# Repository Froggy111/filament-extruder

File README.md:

# Filament Extruder

fully closed loop FDM filameent production machine

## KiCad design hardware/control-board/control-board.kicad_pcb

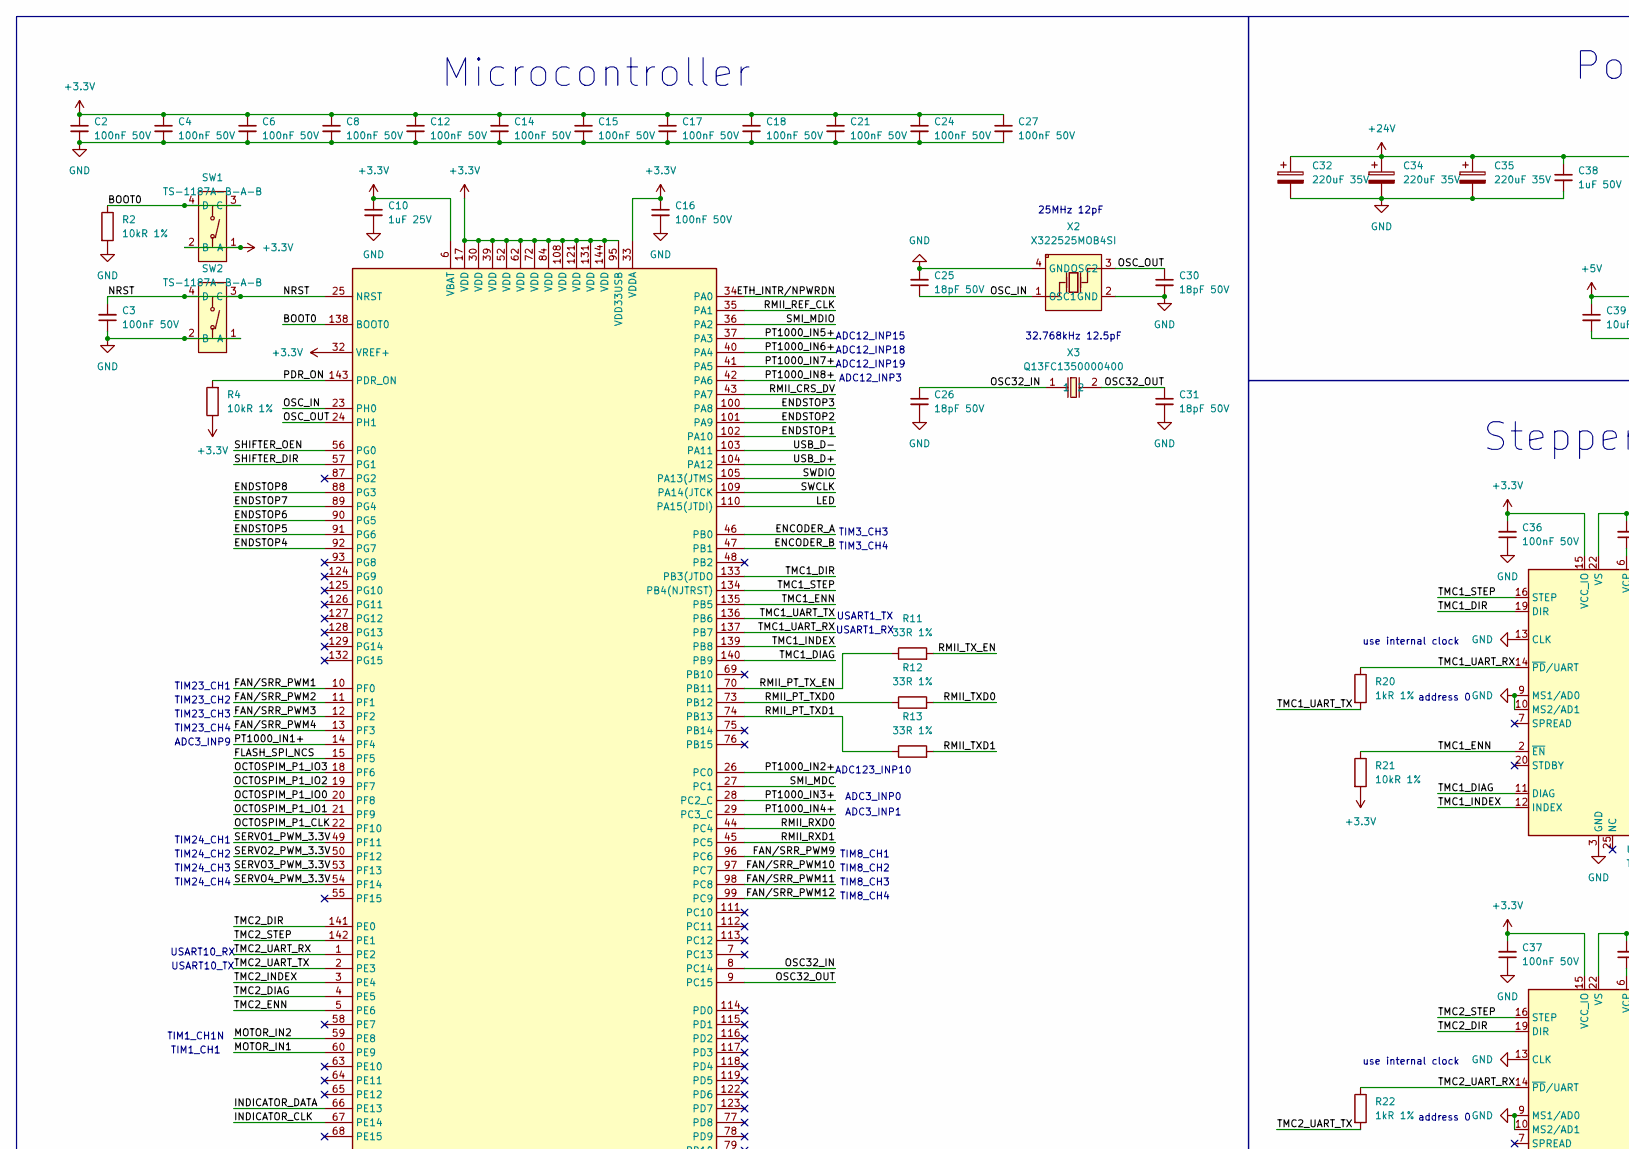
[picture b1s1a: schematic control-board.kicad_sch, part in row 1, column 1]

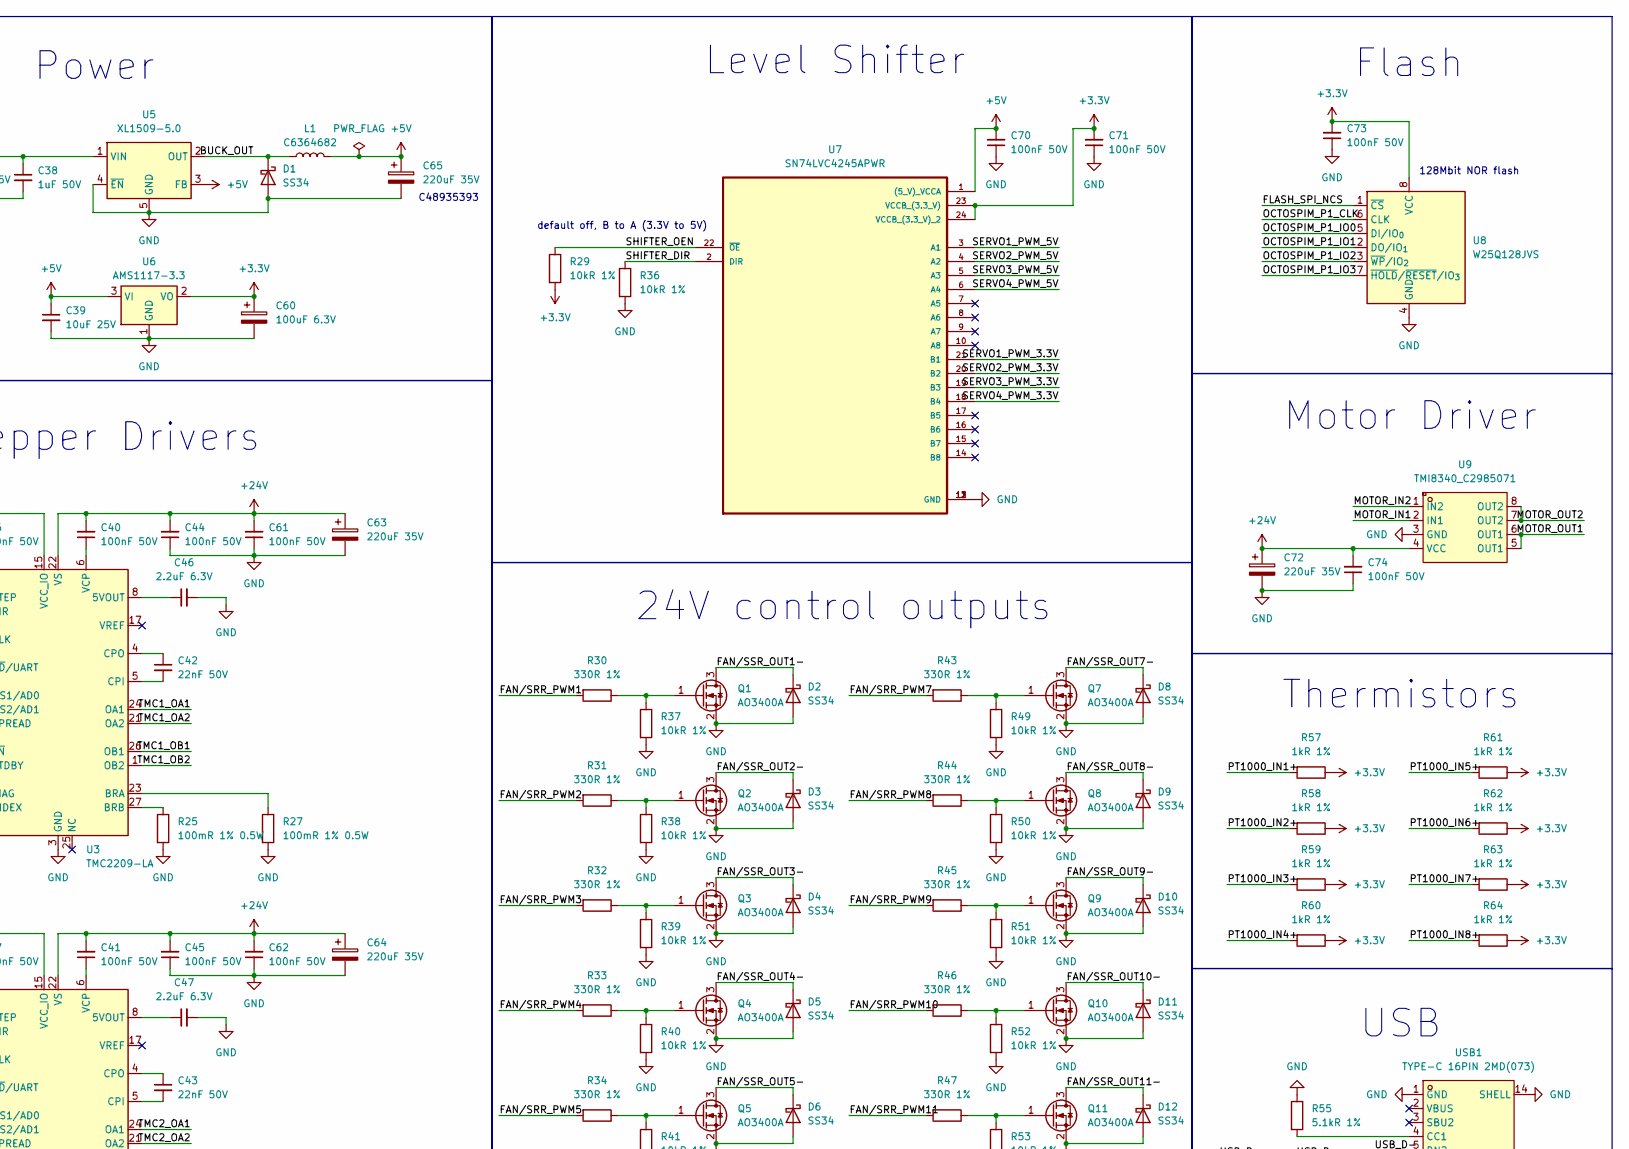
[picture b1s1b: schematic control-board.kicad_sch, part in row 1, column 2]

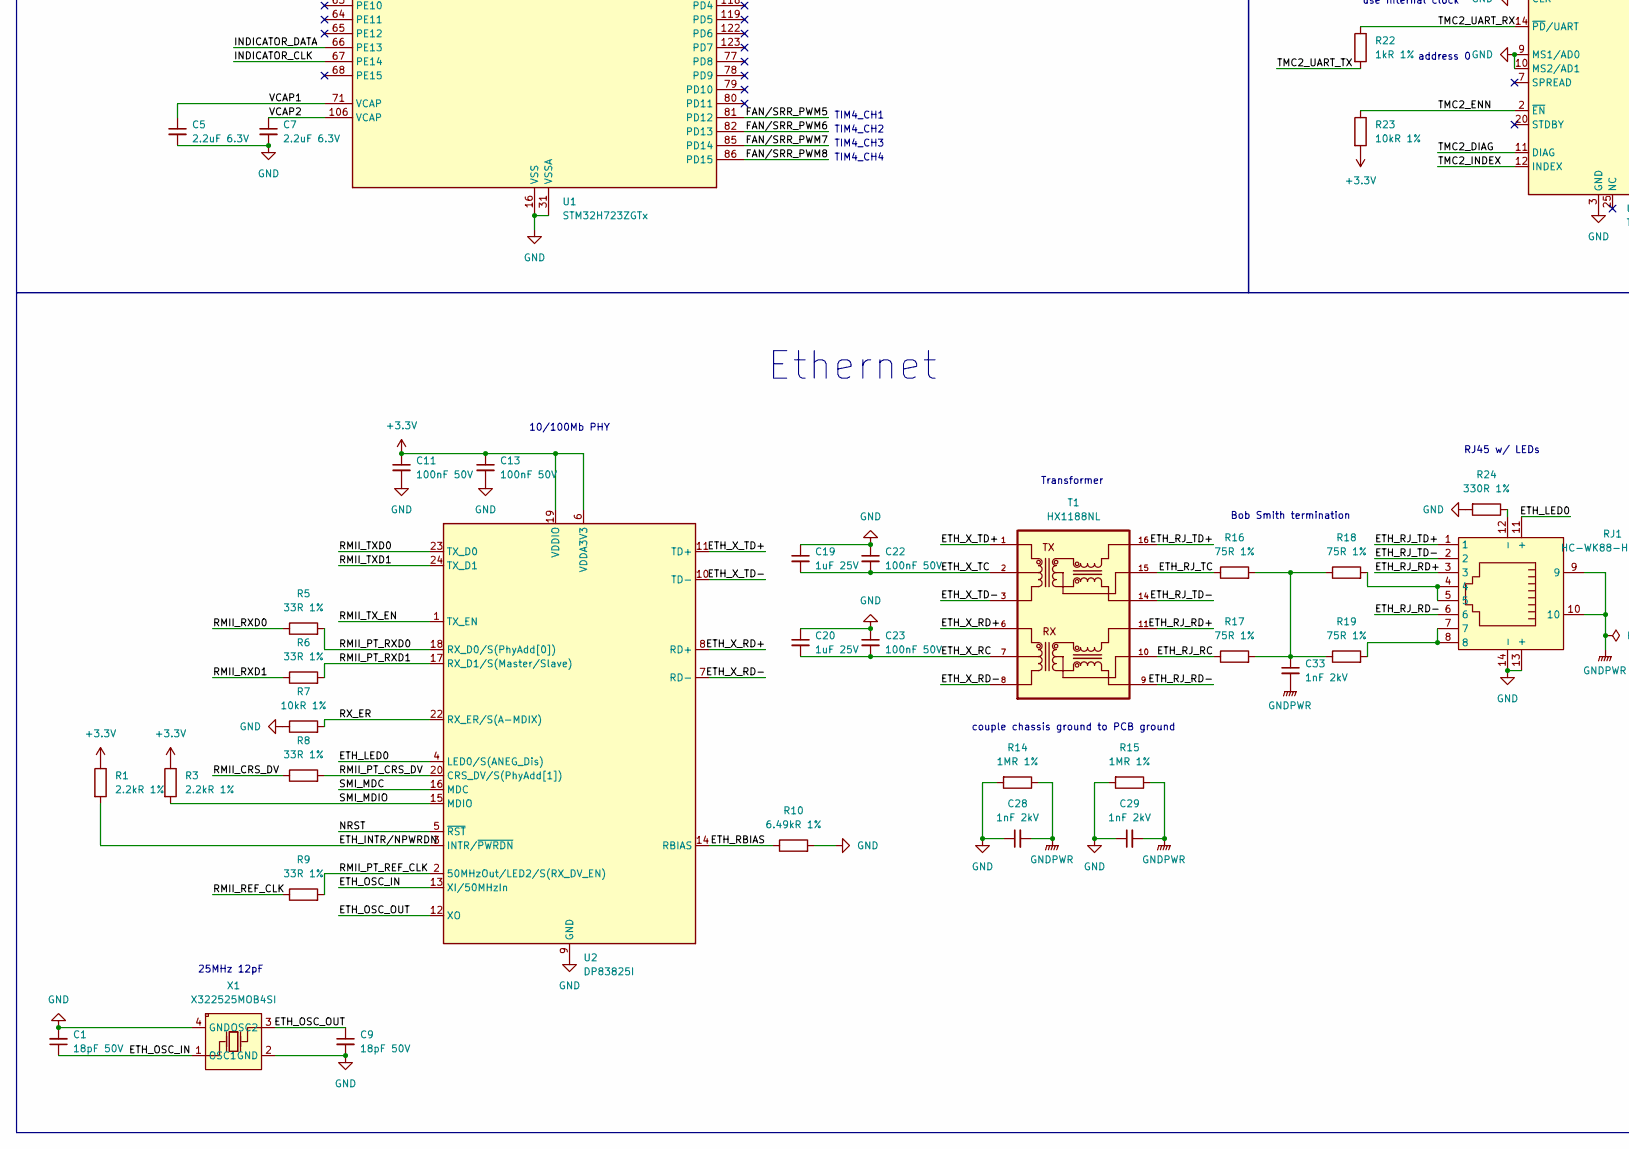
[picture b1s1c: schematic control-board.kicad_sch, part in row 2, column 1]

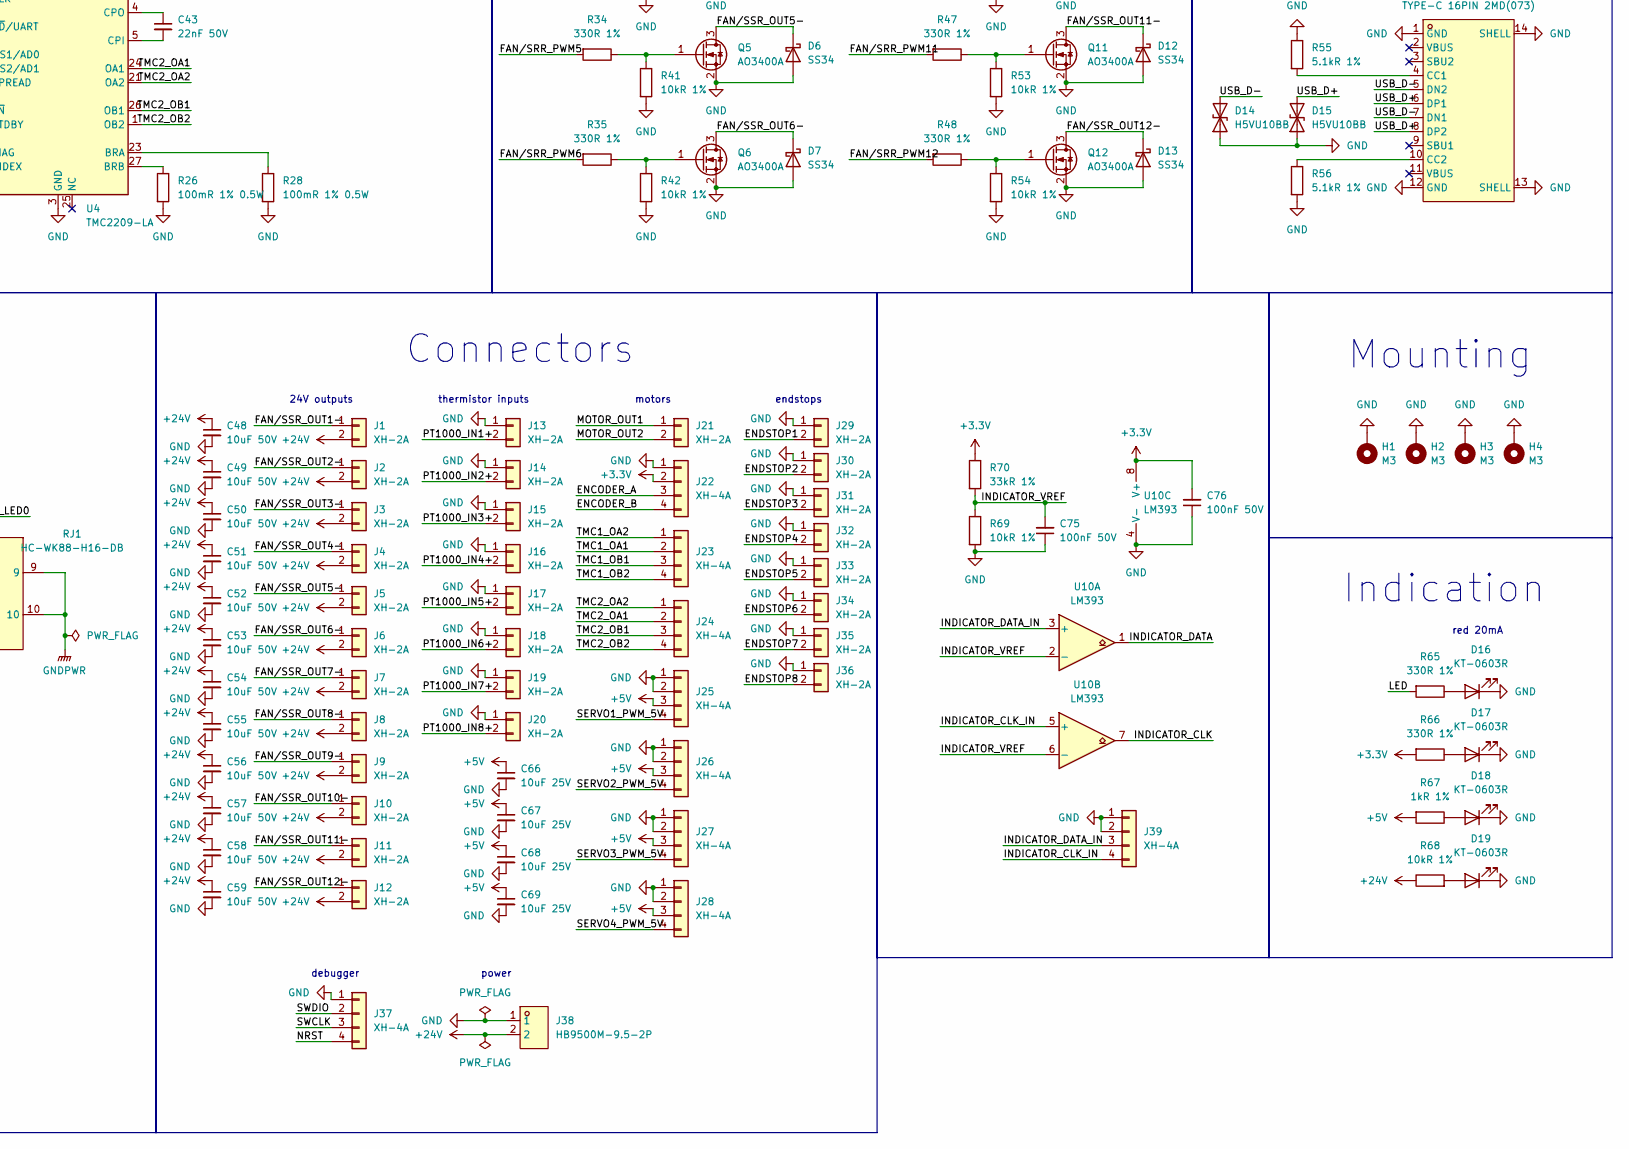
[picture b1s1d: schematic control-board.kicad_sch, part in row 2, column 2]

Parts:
C1, C9, C25, C26, C30, C31: 18pF 50V; C_0402_1005Metric
C2, C3, C4, C6, C8, C11, C12, C13, C14, C15, C16, C17, C18, C21, C22, C23, C24, C27, C36, C37, C40, C41, C44, C45, C61, C62, C70, C71, C73, C74, C75, C76: 100nF 50V; C_0402_1005Metric
C5, C7, C46, C47: 2.2uF 6.3V; C_0402_1005Metric
C10, C19, C20: 1uF 25V; C_0402_1005Metric
C28, C29, C33: 1nF 2kV; C_1206_3216Metric
C32, C34, C35, C63, C64, C65, C72: 220uF 35V; CP_Elec_8x10.5
C38: 1uF 50V; C_0603_1608Metric
C39, C66, C67, C68, C69: 10uF 25V; C_0603_1608Metric
C42, C43: 22nF 50V; C_0402_1005Metric
C48, C49, C50, C51, C52, C53, C54, C55, C56, C57, C58, C59: 10uF 50V; C_1206_3216Metric
C60: 100uF 6.3V; CP_EIA-3528-21_Kemet-B
D1, D2, D3, D4, D5, D6, D7, D8, D9, D10, D11, D12, D13: SS34; D_SMA
D14, D15: H5VU10BB; D_SOD-882
D16, D17, D18, D19: KT-0603R; LED_0603_1608Metric
H1, H2, H3, H4: M3; MountingHole_3.2mm_M3_Pad_Via
J1, J2, J3, J4, J5, J6, J7, J8, J9, J10, J11, J12, J13, J14, J15, J16, J17, J18, J19, J20, J21, J29, J30, J31, J32, J33, J34, J35, J36: XH-2A; JST_XH_B2B-XH-A_1x02_P2.50mm_Vertical
J22, J23, J24, J25, J26, J27, J28, J37, J39: XH-4A; JST_XH_B4B-XH-A_1x04_P2.50mm_Vertical
J38: HB9500M-9.5-2P; CONN-TH_HB9500M-9.5-2P; LCSC Part C601239
L1: C6364682; L_Chilisin_BMRF00101040
Q1, Q2, Q3, Q4, Q5, Q6, Q7, Q8, Q9, Q10, Q11, Q12: AO3400A; SOT-23
R1, R3: 2.2kR 1%; R_0402_1005Metric
R2, R4, R7, R21, R23, R29, R36, R37, R38, R39, R40, R41, R42, R49, R50, R51, R52, R53, R54, R68, R69: 10kR 1%; R_0402_1005Metric
R5, R6, R8, R9, R11, R12, R13: 33R 1%; R_0402_1005Metric
R10: 6.49kR 1%; R_0402_1005Metric
R14, R15: 1MR 1%; R_1206_3216Metric
R16, R17, R18, R19: 75R 1%; R_0402_1005Metric
R20, R22, R57, R58, R59, R60, R61, R62, R63, R64, R67: 1kR 1%; R_0402_1005Metric
R24, R30, R31, R32, R33, R34, R35, R43, R44, R45, R46, R47, R48, R65, R66: 330R 1%; R_0402_1005Metric
R25, R26, R27, R28: 100mR 1% 0.5W; R_1206_3216Metric
R55, R56: 5.1kR 1%; R_0402_1005Metric
R70: 33kR 1%; R_0402_1005Metric
RJ1: HC-WK88-H16-DB; RJ45-TH_HC-WK88-H16-DB; LCSC Part C7501824
SW1, SW2: TS-1187A-B-A-B; SW-SMD_4P-L5.1-W5.1-P3.70-LS6.5-TL_H1.5; LCSC Part C318884
T1: HX1188NL; HXXXX
U1: STM32H723ZGTx; LQFP-144_20x20mm_P0.5mm
U2: DP83825I; Texas_RMQ0024A_WQFN-24-1EP_3x3mm_P0.4mm_EP1.9x1.9mm
U3, U4: TMC2209-LA; VQFN-28-1EP_5x5mm_P0.5mm_EP3.7x3.7mm_ThermalVias
U5: XL1509-5.0; SOIC-8_3.9x4.9mm_P1.27mm
U6: AMS1117-3.3; SOT-223-3_TabPin2
U7: SN74LVC4245APWR; SOP65P640X120-24N
U8: W25Q128JVS; SOIC-8_5.3x5.3mm_P1.27mm
U9: TMI8340_C2985071; SOP-8_L4.9-W3.9-P1.27-LS6.0-BL-1; LCSC Part C2985071
U10: LM393; SOIC-8_3.9x4.9mm_P1.27mm
USB1: TYPE-C 16PIN 2MD(073); USB-C-SMD_TYPE-C-6PIN-2MD-073; LCSC Part C2765186
X1, X2: X322525MOB4SI; CRYSTAL-SMD_4P-L3.2-W2.5-BL; LCSC Part C9006
X3: Q13FC1350000400; FC-135R_L3.2-W1.5; LCSC Part C32346

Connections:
+3.3V: C2.1, C4.1, C6.1, C8.1, C10.1, C11.1, C12.1, C13.1, C14.1, C15.1, C16.1, C17.1, C18.1, C21.1, C24.1, C27.1, C36.2, C37.2, C60.1, C71.2, C73.2, C76.2, J22.2, R1.1, R3.1, R4.1, R21.2, R23.2, R29.2, R57.1, R58.1, R59.1, R60.1, R61.1, R62.1, R63.1, R64.1, R66.2, R70.1, SW1.1 (A), SW1.2 (B), U1.6 (VBAT), U1.17 (VDD), U1.30 (VDD), U1.32 (VREF+), U1.33 (VDDA), U1.39 (VDD), U1.52 (VDD), U1.62 (VDD), U1.72 (VDD), U1.84 (VDD), U1.95 (VDD33USB), U1.108 (VDD), U1.121 (VDD), U1.131 (VDD), U1.144 (VDD), U2.6 (VDDA3V3), U2.19 (VDDIO), U3.15 (VCC_IO), U4.15 (VCC_IO), U6.2 (VO), U7.23 (VCCB_(3.3_V)), U7.24 (VCCB_(3.3_V)_2), U8.8 (VCC), U10.8 (V+)
+5V: C39.1, C65.1, C66.1, C67.1, C68.1, C69.1, C70.2, J25.3, J26.3, J27.3, J28.3, L1.2, R67.2, U5.3 (FB), U6.3 (VI), U7.1 ((5_V)_VCCA)
+24V: C32.1, C34.1, C35.1, C38.1, C40.2, C41.2, C44.2, C45.2, C48.1, C49.1, C50.1, C51.1, C52.1, C53.1, C54.1, C55.1, C56.1, C57.1, C58.1, C59.1, C61.2, C62.2, C63.1, C64.1, C72.1, C74.2, J1.2, J2.2, J3.2, J4.2, J5.2, J6.2, J7.2, J8.2, J9.2, J10.2, J11.2, J12.2, J38.2, R68.1, U3.22 (VS), U3.28 (VS), U4.22 (VS), U4.28 (VS), U5.1 (VIN), U9.4 (VCC)
/BOOT0: R2.1, SW1.3 (C), SW1.4 (D), U1.138 (BOOT0)
/BUCK_OUT: D1.1 (K), L1.1, U5.2 (OUT)
/ENCODER_A: J22.3, U1.46 (PB0)
/ENCODER_B: J22.4, U1.47 (PB1)
/ENDSTOP1: J29.2, U1.102 (PA10)
/ENDSTOP2: J30.2, U1.101 (PA9)
/ENDSTOP3: J31.2, U1.100 (PA8)
/ENDSTOP4: J32.2, U1.92 (PG7)
/ENDSTOP5: J33.2, U1.91 (PG6)
/ENDSTOP6: J34.2, U1.90 (PG5)
/ENDSTOP7: J35.2, U1.89 (PG4)
/ENDSTOP8: J36.2, U1.88 (PG3)
/ETH_INTR/NPWRDN: R1.2, U1.34 (PA0), U2.3 (INTR/~PWRDN)
/ETH_LED0: RJ1.11 (+), U2.4 (LED0/S(ANEG_Dis))
/ETH_OSC_IN: C1.1, U2.13 (XI/50MHzIn), X1.1 (OSC1)
/ETH_OSC_OUT: C9.1, U2.12 (XO), X1.3 (OSC2)
/ETH_RBIAS: R10.1, U2.14 (RBIAS)
/ETH_RJ_RC: R17.1, T1.10
/ETH_RJ_RD+: RJ1.3, T1.11
/ETH_RJ_RD-: RJ1.6, T1.9
/ETH_RJ_TC: R16.1, T1.15
/ETH_RJ_TD+: RJ1.1, T1.16
/ETH_RJ_TD-: RJ1.2, T1.14
/ETH_X_RC: C20.2, C23.2, T1.7
/ETH_X_RD+: T1.6, U2.8 (RD+)
/ETH_X_RD-: T1.8, U2.7 (RD-)
/ETH_X_TC: C19.2, C22.2, T1.2
/ETH_X_TD+: T1.1, U2.11 (TD+)
/ETH_X_TD-: T1.3, U2.10 (TD-)
/FAN/SRR_PWM1: R30.2, U1.10 (PF0)
/FAN/SRR_PWM2: R31.2, U1.11 (PF1)
/FAN/SRR_PWM3: R32.2, U1.12 (PF2)
/FAN/SRR_PWM4: R33.2, U1.13 (PF3)
/FAN/SRR_PWM5: R34.2, U1.81 (PD12)
/FAN/SRR_PWM6: R35.2, U1.82 (PD13)
/FAN/SRR_PWM7: R43.2, U1.85 (PD14)
/FAN/SRR_PWM8: R44.2, U1.86 (PD15)
/FAN/SRR_PWM9: R45.2, U1.96 (PC6)
/FAN/SRR_PWM10: R46.2, U1.97 (PC7)
/FAN/SRR_PWM11: R47.2, U1.98 (PC8)
/FAN/SRR_PWM12: R48.2, U1.99 (PC9)
/FAN/SSR_OUT1-: D2.1 (K), J1.1, Q1.3 (D)
/FAN/SSR_OUT2-: D3.1 (K), J2.1, Q2.3 (D)
/FAN/SSR_OUT3-: D4.1 (K), J3.1, Q3.3 (D)
/FAN/SSR_OUT4-: D5.1 (K), J4.1, Q4.3 (D)
/FAN/SSR_OUT5-: D6.1 (K), J5.1, Q5.3 (D)
/FAN/SSR_OUT6-: D7.1 (K), J6.1, Q6.3 (D)
/FAN/SSR_OUT7-: D8.1 (K), J7.1, Q7.3 (D)
/FAN/SSR_OUT8-: D9.1 (K), J8.1, Q8.3 (D)
/FAN/SSR_OUT9-: D10.1 (K), J9.1, Q9.3 (D)
/FAN/SSR_OUT10-: D11.1 (K), J10.1, Q10.3 (D)
/FAN/SSR_OUT11-: D12.1 (K), J11.1, Q11.3 (D)
/FAN/SSR_OUT12-: D13.1 (K), J12.1, Q12.3 (D)
/FLASH_SPI_NCS: U1.15 (PF5), U8.1 (~CS)
/INDICATOR_CLK: U1.67 (PE14), U10.7
/INDICATOR_CLK_IN: J39.4, U10.5 (+)
/INDICATOR_DATA: U1.66 (PE13), U10.1
/INDICATOR_DATA_IN: J39.3, U10.3 (+)
/INDICATOR_VREF: C75.2, R69.1, R70.2, U10.2 (-), U10.6 (-)
/LED: R65.2, U1.110 (PA15(JTDI))
/MOTOR_IN1: U1.60 (PE9), U9.2 (IN1)
/MOTOR_IN2: U1.59 (PE8), U9.1 (IN2)
/MOTOR_OUT1: J21.1, U9.5 (OUT1), U9.6 (OUT1)
/MOTOR_OUT2: J21.2, U9.7 (OUT2), U9.8 (OUT2)
/NRST: C3.2, J37.4, SW2.3 (C), SW2.4 (D), U1.25 (NRST), U2.5 (~RST)
/OCTOSPIM_P1_CLK: U1.22 (PF10), U8.6 (CLK)
/OCTOSPIM_P1_IO0: U1.20 (PF8), U8.5 (DI/IO_{0})
/OCTOSPIM_P1_IO1: U1.21 (PF9), U8.2 (DO/IO_{1})
/OCTOSPIM_P1_IO2: U1.19 (PF7), U8.3 (~WP/IO_{2})
/OCTOSPIM_P1_IO3: U1.18 (PF6), U8.7 (~HOLD/~RESET/IO_{3})
/OSC32_IN: C26.1, U1.8 (PC14), X3.1
/OSC32_OUT: C31.1, U1.9 (PC15), X3.2
/OSC_IN: C25.1, U1.23 (PH0), X2.1 (OSC1)
/OSC_OUT: C30.1, U1.24 (PH1), X2.3 (OSC2)
/PDR_ON: R4.2, U1.143 (PDR_ON)
/PT1000_IN1+: J13.2, R57.2, U1.14 (PF4)
/PT1000_IN2+: J14.2, R58.2, U1.26 (PC0)
/PT1000_IN3+: J15.2, R59.2, U1.28 (PC2_C)
/PT1000_IN4+: J16.2, R60.2, U1.29 (PC3_C)
/PT1000_IN5+: J17.2, R61.2, U1.37 (PA3)
/PT1000_IN6+: J18.2, R62.2, U1.40 (PA4)
/PT1000_IN7+: J19.2, R63.2, U1.41 (PA5)
/PT1000_IN8+: J20.2, R64.2, U1.42 (PA6)
/RMII_CRS_DV: R8.1, U1.43 (PA7)
/RMII_PT_CRS_DV: R8.2, U2.20 (CRS_DV/S(PhyAdd[1]))
/RMII_PT_REF_CLK: R9.2, U2.2 (50MHzOut/LED2/S(RX_DV_EN))
/RMII_PT_RXD0: R5.2, U2.18 (RX_D0/S(PhyAdd[0]))
/RMII_PT_RXD1: R6.2, U2.17 (RX_D1/S(Master/Slave))
/RMII_PT_TXD0: R12.1, U1.73 (PB12)
/RMII_PT_TXD1: R13.1, U1.74 (PB13)
/RMII_PT_TX_EN: R11.1, U1.70 (PB11)
/RMII_REF_CLK: R9.1, U1.35 (PA1)
/RMII_RXD0: R5.1, U1.44 (PC4)
/RMII_RXD1: R6.1, U1.45 (PC5)
/RMII_TXD0: R12.2, U2.23 (TX_D0)
/RMII_TXD1: R13.2, U2.24 (TX_D1)
/RMII_TX_EN: R11.2, U2.1 (TX_EN)
/RX_ER: R7.2, U2.22 (RX_ER/S(A-MDIX))
/SERVO1_PWM_3.3V: U1.49 (PF11), U7.21 (B1)
/SERVO1_PWM_5V: J25.4, U7.3 (A1)
/SERVO2_PWM_3.3V: U1.50 (PF12), U7.20 (B2)
/SERVO2_PWM_5V: J26.4, U7.4 (A2)
/SERVO3_PWM_3.3V: U1.53 (PF13), U7.19 (B3)
/SERVO3_PWM_5V: J27.4, U7.5 (A3)
/SERVO4_PWM_3.3V: U1.54 (PF14), U7.18 (B4)
/SERVO4_PWM_5V: J28.4, U7.6 (A4)
/SHIFTER_DIR: R36.1, U1.57 (PG1), U7.2 (DIR)
/SHIFTER_OEN: R29.1, U1.56 (PG0), U7.22 (~OE)
/SMI_MDC: U1.27 (PC1), U2.16 (MDC)
/SMI_MDIO: R3.2, U1.36 (PA2), U2.15 (MDIO)
/SWCLK: J37.3, U1.109 (PA14(JTCK)
/SWDIO: J37.2, U1.105 (PA13(JTMS)
/TMC1_DIAG: U1.140 (PB9), U3.11 (DIAG)
/TMC1_DIR: U1.133 (PB3(JTDO), U3.19 (DIR)
/TMC1_ENN: R21.1, U1.135 (PB5), U3.2 (~EN)
/TMC1_INDEX: U1.139 (PB8), U3.12 (INDEX)
/TMC1_OA1: J23.2, U3.24 (OA1)
/TMC1_OA2: J23.1, U3.21 (OA2)
/TMC1_OB1: J23.3, U3.26 (OB1)
/TMC1_OB2: J23.4, U3.1 (OB2)
/TMC1_STEP: U1.134 (PB4(NJTRST)), U3.16 (STEP)
/TMC1_UART_RX: R20.1, U1.137 (PB7), U3.14 (~PD/UART)
/TMC1_UART_TX: R20.2, U1.136 (PB6)
/TMC2_DIAG: U1.4 (PE5), U4.11 (DIAG)
/TMC2_DIR: U1.141 (PE0), U4.19 (DIR)
/TMC2_ENN: R23.1, U1.5 (PE6), U4.2 (~EN)
/TMC2_INDEX: U1.3 (PE4), U4.12 (INDEX)
/TMC2_OA1: J24.2, U4.24 (OA1)
/TMC2_OA2: J24.1, U4.21 (OA2)
/TMC2_OB1: J24.3, U4.26 (OB1)
/TMC2_OB2: J24.4, U4.1 (OB2)
/TMC2_STEP: U1.142 (PE1), U4.16 (STEP)
/TMC2_UART_RX: R22.1, U1.1 (PE2), U4.14 (~PD/UART)
/TMC2_UART_TX: R22.2, U1.2 (PE3)
/USB_D+: D15.2 (A2), U1.104 (PA12), USB1.6 (DP1), USB1.8 (DP2)
/USB_D-: D14.2 (A2), U1.103 (PA11), USB1.5 (DN2), USB1.7 (DN1)
/VCAP1: C5.1, U1.71 (VCAP)
/VCAP2: C7.1, U1.106 (VCAP)
GND: C1.2, C2.2, C3.1, C4.2, C5.2, C6.2, C7.2, C8.2, C9.2, C10.2, C11.2, C12.2, C13.2, C14.2, C15.2, C16.2, C17.2, C18.2, C19.1, C20.1, C21.2, C22.1, C23.1, C24.2, C25.2, C26.2, C27.2, C28.1, C29.1, C30.2, C31.2, C32.2, C34.2, C35.2, C36.1, C37.1, C38.2, C39.2, C44.1, C45.1, C46.2, C47.2, C48.2, C49.2, C50.2, C51.2, C52.2, C53.2, C54.2, C55.2, C56.2, C57.2, C58.2, C59.2, C60.2, C61.1, C62.1, C63.2, C64.2, C65.2, C66.2, C67.2, C68.2, C69.2, C70.1, C71.1, C72.2, C73.1, C74.1, C75.1, C76.1, D1.2 (A), D2.2 (A), D3.2 (A), D4.2 (A), D5.2 (A), D6.2 (A), D7.2 (A), D8.2 (A), D9.2 (A), D10.2 (A), D11.2 (A), D12.2 (A), D13.2 (A), D14.1 (A1), D15.1 (A1), D16.1 (K), D17.1 (K), D18.1 (K), D19.1 (K), H1.1, H2.1, H3.1, H4.1, J13.1, J14.1, J15.1, J16.1, J17.1, J18.1, J19.1, J20.1, J22.1, J25.1, J25.2, J26.1, J26.2, J27.1, J27.2, J28.1, J28.2, J29.1, J30.1, J31.1, J32.1, J33.1, J34.1, J35.1, J36.1, J37.1, J38.1, J39.1, J39.2, Q1.2 (S), Q2.2 (S), Q3.2 (S), Q4.2 (S), Q5.2 (S), Q6.2 (S), Q7.2 (S), Q8.2 (S), Q9.2 (S), Q10.2 (S), Q11.2 (S), Q12.2 (S), R2.2, R7.1, R10.2, R14.2, R15.2, R24.2, R25.2, R26.2, R27.2, R28.2, R36.2, R37.2, R38.2, R39.2, R40.2, R41.2, R42.2, R49.2, R50.2, R51.2, R52.2, R53.2, R54.2, R55.1, R56.2, R69.2, RJ1.13 (+), RJ1.14 (-), SW2.1 (A), SW2.2 (B), U1.16 (VSS), U1.31 (VSSA), U1.38 (VSS), U1.51 (VSS), U1.61 (VSS), U1.83 (VSS), U1.94 (VSS), U1.107 (VSS), U1.120 (VSS), U1.130 (VSS), U2.9 (GND), U2.21 (GND), U2.25 (GND), U3.3 (GND), U3.9 (MS1/AD0), U3.10 (MS2/AD1), U3.13 (CLK), U3.18 (GND), U3.29 (GND), U4.3 (GND), U4.9 (MS1/AD0), U4.10 (MS2/AD1), U4.13 (CLK), U4.18 (GND), U4.29 (GND), U5.4 (~EN), U5.5 (GND), U5.6 (GND), U5.7 (GND), U5.8 (GND), U6.1 (GND), U7.11 (GND), U7.12 (GND), U7.13 (GND), U8.4 (GND), U9.3 (GND), U10.4 (V-), USB1.1 (GND), USB1.12 (GND), USB1.13 (SHELL), USB1.14 (SHELL), X1.2 (GND), X1.4 (GND), X2.2 (GND), X2.4 (GND)
GNDPWR: C28.2, C29.2, C33.2, R14.1, R15.1, RJ1.9, RJ1.10
unnamed: C33.1, R16.2, R17.2, R18.1, R19.1
unnamed: D16.2 (A), R65.1
unnamed: D17.2 (A), R66.1
unnamed: D18.2 (A), R67.1
unnamed: D19.2 (A), R68.2
unnamed: Q1.1 (G), R30.1, R37.1
unnamed: Q2.1 (G), R31.1, R38.1
unnamed: Q3.1 (G), R32.1, R39.1
unnamed: Q4.1 (G), R33.1, R40.1
unnamed: Q5.1 (G), R34.1, R41.1
unnamed: Q6.1 (G), R35.1, R42.1
unnamed: Q7.1 (G), R43.1, R49.1
unnamed: Q8.1 (G), R44.1, R50.1
unnamed: Q9.1 (G), R45.1, R51.1
unnamed: Q10.1 (G), R46.1, R52.1
unnamed: Q11.1 (G), R47.1, R53.1
unnamed: Q12.1 (G), R48.1, R54.1
unnamed: R18.2, RJ1.4, RJ1.5
unnamed: R19.2, RJ1.7, RJ1.8
unnamed: R24.1, RJ1.12 (-)
unnamed: C46.1, U3.8 (5VOUT)
unnamed: R27.1, U3.23 (BRA)
unnamed: R25.1, U3.27 (BRB)
unnamed: C42.2, U3.5 (CPI)
unnamed: C42.1, U3.4 (CPO)
unnamed: C40.1, U3.6 (VCP)
unnamed: C47.1, U4.8 (5VOUT)
unnamed: R28.1, U4.23 (BRA)
unnamed: R26.1, U4.27 (BRB)
unnamed: C43.2, U4.5 (CPI)
unnamed: C43.1, U4.4 (CPO)
unnamed: C41.1, U4.6 (VCP)
unnamed: R55.2, USB1.4 (CC1)
unnamed: R56.1, USB1.10 (CC2)

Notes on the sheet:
TIM3_CH3
Indication
use internal clock
Power
address 0
TIM23_CH3
TIM8_CH4
25MHz 12pF
Connectors
TIM24_CH2
ADC3_INP0
TIM1_CH1
ADC3_INP1
TIM4_CH1
128Mbit NOR flash
TIM8_CH2
ADC12_INP3
TIM8_CH1
TIM1_CH1N
32.768kHz 12.5pF
ADC12_INP15
ADC3_INP9
24V control outputs
Microcontroller
C48935393
USART1_RX
TIM4_CH2
Bob Smith termination
24V outputs
USART10_TX
Level Shifter
10/100Mb PHY
Ethernet
USART10_RX
TIM8_CH3
Motor Driver
TIM4_CH3
TIM24_CH4
TIM23_CH1
Thermistors

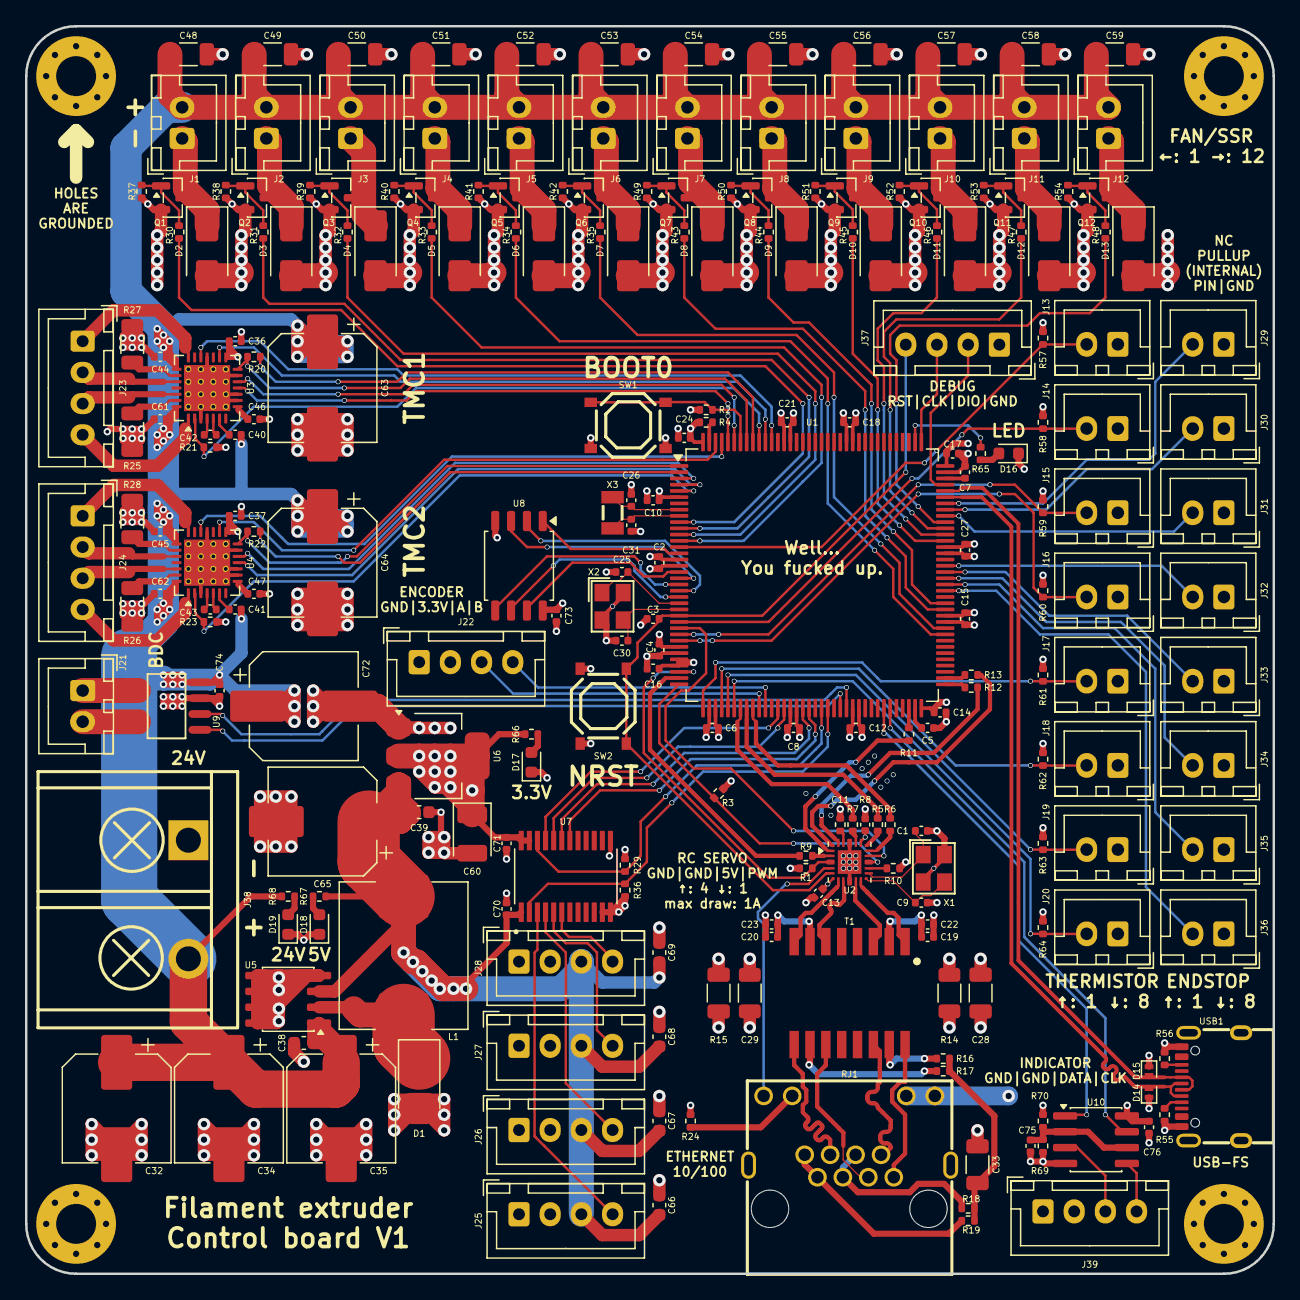
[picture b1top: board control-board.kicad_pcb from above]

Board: 4 copper layers, 100.0 x 100.0 mm, 239 parts (0 on the bottom side), 177 nets.

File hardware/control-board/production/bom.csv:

Designator,Footprint,Quantity,Value,LCSC Part #
"C1, C25, C26, C30, C31, C9",0402,6,18pF 50V,
"C10, C19, C20",0402,3,1uF 25V,
"C11, C12, C13, C14, C15, C16, C17, C18, C2, C21, C22, C23, C24, C27, C3, C36, C37, C4, C40, C41, C44, C45, C6, C61, C62, C70, C71, C73, C74, C75, C76, C8",0402,32,100nF 50V,
"C28, C29, C33",1206,3,1nF 2kV,
"C32, C34, C35, C63, C64, C65, C72",CP_Elec_8x10.5,7,220uF 35V,
C38,0603,1,1uF 50V,
"C39, C66, C67, C68, C69",0603,5,10uF 25V,
"C42, C43",0402,2,22nF 50V,
"C46, C47, C5, C7",0402,4,2.2uF 6.3V,
"C48, C49, C50, C51, C52, C53, C54, C55, C56, C57, C58, C59",1206,12,10uF 50V,
C60,CP_EIA-3528-21_Kemet-B,1,100uF 6.3V,
"D1, D10, D11, D12, D13, D2, D3, D4, D5, D6, D7, D8, D9",D_SMA,13,SS34,
"D14, D15",D_SOD-882,2,H5VU10BB,
"D16, D17, D18, D19",0603,4,KT-0603R,
"J1, J10, J11, J12, J13, J14, J15, J16, J17, J18, J19, J2, J20, J21, J29, J3, J30, J31, J32, J33, J34, J35, J36, J4, J5, J6, J7, J8, J9",JST_XH_B2B-XH-A_1x02_P2.50mm_Vertical,29,XH-2A,
"J22, J23, J24, J25, J26, J27, J28, J37, J39",JST_XH_B4B-XH-A_1x04_P2.50mm_Vertical,9,XH-4A,
J38,CONN-TH_HB9500M-9.5-2P,1,HB9500M-9.5-2P,C601239
L1,L_Chilisin_BMRF00101040,1,C6364682,
"Q1, Q10, Q11, Q12, Q2, Q3, Q4, Q5, Q6, Q7, Q8, Q9",SOT-23,12,AO3400A,
"R1, R3",0402,2,2.2kR 1%,
R10,0402,1,6.49kR 1%,
"R11, R12, R13, R5, R6, R8, R9",0402,7,33R 1%,
"R14, R15",1206,2,1MR 1%,
"R16, R17, R18, R19",0402,4,75R 1%,
"R2, R21, R23, R29, R36, R37, R38, R39, R4, R40, R41, R42, R49, R50, R51, R52, R53, R54, R68, R69, R7",0402,21,10kR 1%,
"R20, R22, R57, R58, R59, R60, R61, R62, R63, R64, R67",0402,11,1kR 1%,
"R24, R30, R31, R32, R33, R34, R35, R43, R44, R45, R46, R47, R48, R65, R66",0402,15,330R 1%,
"R25, R26, R27, R28",1206,4,100mR 1% 0.5W,
"R55, R56",0402,2,5.1kR 1%,
R70,0402,1,33kR 1%,
RJ1,RJ45-TH_HC-WK88-H16-DB,1,HC-WK88-H16-DB,C7501824
"SW1, SW2",SW-SMD_4P-L5.1-W5.1-P3.70-LS6.5-TL_H1.5,2,TS-1187A-B-A-B,C318884
T1,HXXXX,1,HX1188NL,
U1,LQFP-144_20x20mm_P0.5mm,1,STM32H723ZGTx,
U10,SOIC-8_3.9x4.9mm_P1.27mm,1,LM393,
U2,Texas_RMQ0024A_WQFN-24-1EP_3x3mm_P0.4mm_EP1.9x1.9mm,1,DP83825I,
"U3, U4",VQFN-28-1EP_5x5mm_P0.5mm_EP3.7x3.7mm_ThermalVias,2,TMC2209-LA,
U5,SOIC-8_3.9x4.9mm_P1.27mm,1,XL1509-5.0,
U6,SOT-223-3_TabPin2,1,AMS1117-3.3,
U7,SOP65P640X120-24N,1,SN74LVC4245APWR,
U8,SOIC-8_5.3x5.3mm_P1.27mm,1,W25Q128JVS,
U9,SOP-8_L4.9-W3.9-P1.27-LS6.0-BL-1,1,TMI8340_C2985071,C2985071
USB1,USB-C-SMD_TYPE-C-6PIN-2MD-073,1,TYPE-C 16PIN 2MD(073),C2765186
"X1, X2",CRYSTAL-SMD_4P-L3.2-W2.5-BL,2,X322525MOB4SI,C9006
X3,FC-135R_L3.2-W1.5,1,Q13FC1350000400,C32346

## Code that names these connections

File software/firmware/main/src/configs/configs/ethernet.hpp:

#pragma once

#include "gpio.hpp"

const gpio::PinConfig RMII_REF_CLK_PIN = {GPIOA, gpio::Pin::PIN1,
                                          gpio::AF::AF11_ETH};
const gpio::PinConfig RMII_CRS_DV_PIN = {GPIOA, gpio::Pin::PIN7,
                                         gpio::AF::AF11_ETH};
const gpio::PinConfig RMII_TX_EN_PIN = {GPIOB, gpio::Pin::PIN11,
                                        gpio::AF::AF11_ETH};
const gpio::PinConfig RMII_TXD0_PIN = {GPIOB, gpio::Pin::PIN12,
                                       gpio::AF::AF11_ETH};
const gpio::PinConfig RMII_TXD1_PIN = {GPIOB, gpio::Pin::PIN13,
                                       gpio::AF::AF11_ETH};
const gpio::PinConfig RMII_RXD0_PIN = {GPIOC, gpio::Pin::PIN4,
                                       gpio::AF::AF11_ETH};
const gpio::PinConfig RMII_RXD1_PIN = {GPIOC, gpio::Pin::PIN5,
                                       gpio::AF::AF11_ETH};
const gpio::PinConfig SMI_MDIO_PIN = {GPIOA, gpio::Pin::PIN2,
                                      gpio::AF::AF11_ETH};
const gpio::PinConfig SMI_MDC_PIN = {GPIOC, gpio::Pin::PIN1,
                                     gpio::AF::AF11_ETH};

const uint16_t PHY_BSR = 0x01;
const uint16_t PHY_LINK_STATUS = 0x0004;

const uint8_t IPV4_ADDR[4] = {192, 168, 1, 100};
const uint8_t IPV4_MASK[4] = {255, 255, 255, 0};
const uint8_t IPV4_GATEWAY[4] = {192, 168, 1, 1};

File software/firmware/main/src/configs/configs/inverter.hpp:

#pragma once

#include <stdint.h>
#include <stm32g4xx_hal.h>

#include "gpio.hpp"

/**
 * @brief PWM peripheral settings.
 */
// PWM resolution must be above 1 << PWM_MIN_RESOLUTION. This is prioritised
// over frequency deviation
const uint32_t PWM_MIN_RESOLUTION = 6;  // 6 bits of resolution at minimum
// PWM frequency is as far as possible maintained to deviate less than
// PWM_MAX_FREQ_DEVIATION
const float PWM_MAX_FREQ_DEVIATION = 0.05;  // 5% max deviation

// Configuration for drive phase
#define INVERTER_TIMER TIM1  // U, V, W phases on TIM1
#define INVERTER_CLOCK PCLK2
#define PCLK1 1
#define PCLK2 2

#define U_PHASE_CHANNEL TIM_CHANNEL_1
#define V_PHASE_CHANNEL TIM_CHANNEL_3
#define W_PHASE_CHANNEL TIM_CHANNEL_2

/**
 * PC13     ------> TIM1_CH1N (AF4)
 * PB1     ------> TIM1_CH3N (AF6)
 * PB14     ------> TIM1_CH2N (AF6)
 * PA8     ------> TIM1_CH1 (AF6)
 * PA9     ------> TIM1_CH2 (AF6)
 * PA10     ------> TIM1_CH3 (AF6)
 */

// INFO : comment out for drivers that do not use complementary PWM
#define INVERTER_COMPLEMENTARY_PWM

// --- Inverter Leg U (High and Low Side) ---
const gpio::PinConfig INVERTER_U = {GPIOE, gpio::Pin::PIN9, gpio::AF::AF2_TIM1};
const gpio::PinConfig INVERTER_U_N = {GPIOE, gpio::Pin::PIN8,
                                      gpio::AF::AF2_TIM1};

// --- Inverter Leg W (High and Low Side) ---
const gpio::PinConfig INVERTER_V = {GPIOE, gpio::Pin::PIN13,
                                    gpio::AF::AF2_TIM1};
const gpio::PinConfig INVERTER_V_N = {GPIOE, gpio::Pin::PIN12,
                                      gpio::AF::AF2_TIM1};

// --- Inverter Leg V (High and Low Side) ---
const gpio::PinConfig INVERTER_W = {GPIOE, gpio::Pin::PIN11,
                                    gpio::AF::AF2_TIM1};
const gpio::PinConfig INVERTER_W_N = {GPIOE, gpio::Pin::PIN10,
                                      gpio::AF::AF2_TIM1};

const uint32_t INVERTER_BREAKTIME = 500;  // in ns

const uint32_t ADC_CONVERSION_TIME = 1350;  // in ns
const uint32_t ADC_TRIGGER_PRE_OFFSET_TIME = ADC_CONVERSION_TIME / 2;
const uint32_t MIN_TRIGGER_CYCLES = 10;  // clamp to ensure no underflow

// INFO : comment out for drivers without such features

// #define INVERTER_USE_DRIVER_MODE

// maximum high-side on-time, due to bootstrap circuit used
const float MAX_PWM_ONTIME = 0.95;  // 95% should be safe

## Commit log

2025-11-30 added README
2025-12-03 control board complete
2025-12-03 added indicator I/O, text labels
2025-12-03 production files
2025-12-03 changed ethernet termination capacitors to 1nF
2026-01-01 led blinks
2026-01-02 usb detected but hangs
2026-01-02 usb works (got rid of flushing thing)
2026-01-28 FAN/SSR control
2026-01-28 fan off below
2026-01-31 tmc2209 UART conf
2026-02-01 stepper timer
2026-02-02 encoder
2026-02-02 motor
2026-02-09 thermistor
2026-02-09 thermistor fixed
2026-02-09 cleanup
2026-02-09 spooler
2026-02-09 self linker script
2026-02-10 ethernet
2026-02-17 webpage + heater + puller
